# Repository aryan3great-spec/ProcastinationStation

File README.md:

Hello hello hello , this is the start to my hopefully long line of emulators that i hope to perfect to my comfort. 
I love Pokemon hence im here to make a emulator thats gameboy shaped, it is powered by the raspberry pi and i have made 
a custom enclosure for it as well 

I got the inspiration from multiple videos on youtube and also from my friend buying a used new 3ds (terrible naming) and that got me so interested in emulators. From the videos ik that the most cost effiecent and easy to start with sbc is going to be the rpi 02w. 

The only function it has is to run retropie and as many emulators i can fit on a sd card

It has a dpad, abxy, start select and 4 shoulder buttons which should be able to cover emsot games. Which i hope look greaat on the 2.8 inch non touch lcd i've chosen to save cost 

I had some troubles in kicad with locating the buttons equidistant and allign and im certain they arent even symmetric but we'll know soon enough 

i hope to add audio and power in further itterations but idek if i can make the screen work yet so thats why its not as complicated

*THIS WILL BE THE DESIGN OF MY CONSOLE* 

*THIS IS THE PCB DESIGN* 

*THIS IS THE SCHEMATIC*

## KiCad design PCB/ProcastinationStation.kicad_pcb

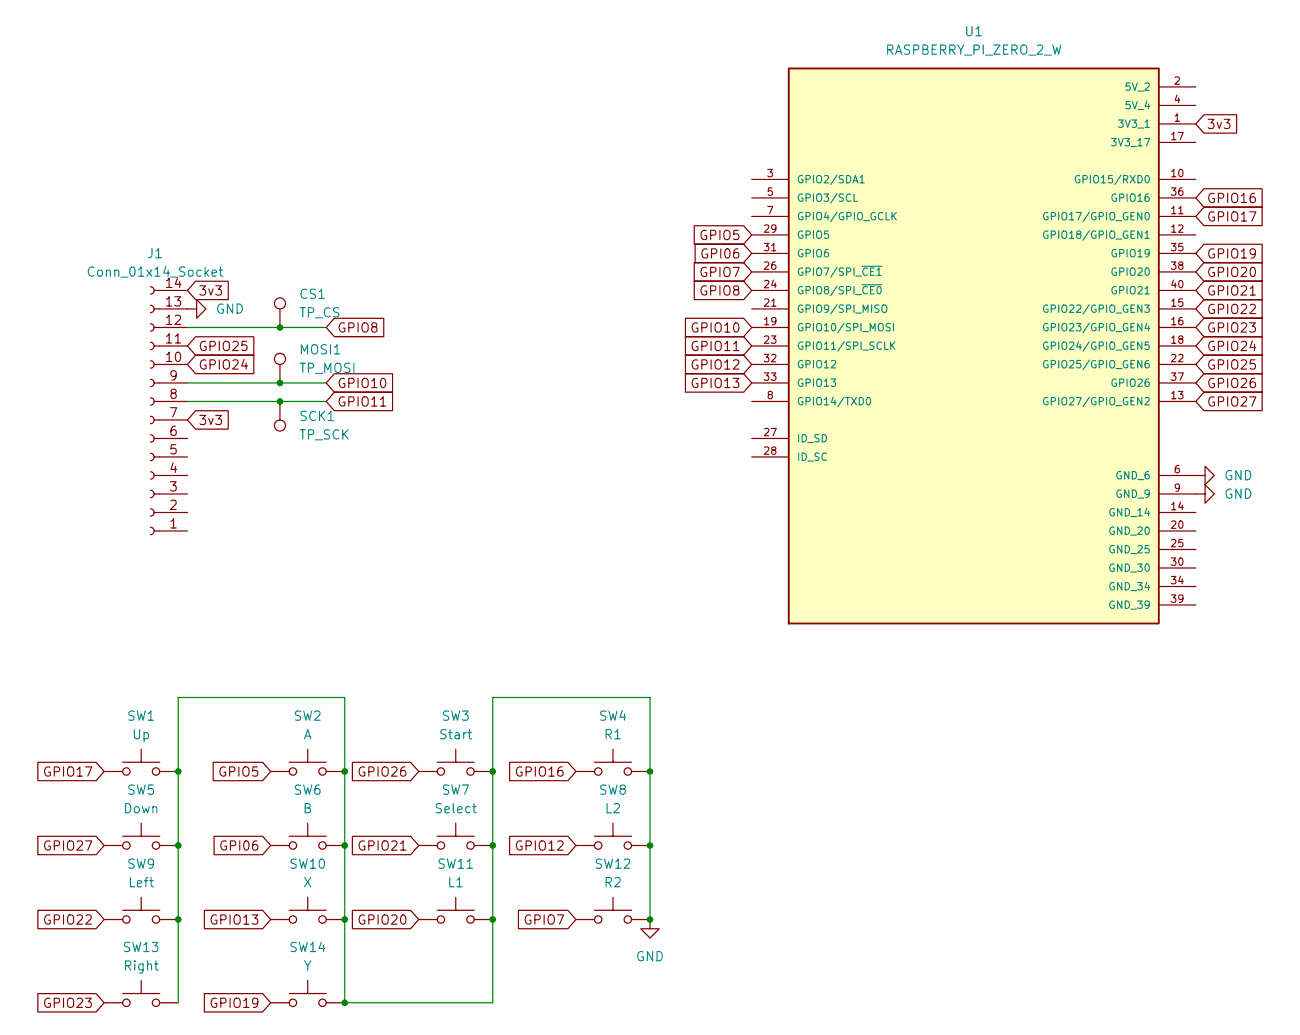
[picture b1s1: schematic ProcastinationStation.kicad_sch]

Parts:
CS1: TP_CS; TestPoint_Pad_D1.0mm
J1: Conn_01x14_Socket; TFT 2.8_ display
MOSI1: TP_MOSI; TestPoint_Pad_D1.0mm
SCK1: TP_SCK; TestPoint_Pad_D1.0mm
SW1: Up; SW_PUSH_6mm_H5mm
SW2: A; SW_PUSH_6mm_H5mm
SW3: Start; SW_PUSH_6mm_H5mm
SW4: R1; SW_PUSH_6mm_H5mm
SW5: Down; SW_PUSH_6mm_H5mm
SW6: B; SW_PUSH_6mm_H5mm
SW7: Select; SW_PUSH_6mm_H5mm
SW8: L2; SW_PUSH_6mm_H5mm
SW9: Left; SW_PUSH_6mm_H5mm
SW10: X; SW_PUSH_6mm_H5mm
SW11: L1; SW_PUSH_6mm_H5mm
SW12: R2; SW_PUSH_6mm_H5mm
SW13: Right; SW_PUSH_6mm_H5mm
SW14: Y; SW_PUSH_6mm_H5mm
U1: RASPBERRY_PI_ZERO_2_W; MODULE_RASPBERRY_PI_ZERO_2_W; PARTREV April 2024

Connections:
3v3: J1.7, J1.14, U1.1 (3V3_1)
GND: J1.13, SW1.2, SW2.2, SW3.2, SW4.2, SW5.2, SW6.2, SW7.2, SW8.2, SW9.2, SW10.2, SW11.2, SW12.2, SW13.2, SW14.2, U1.6 (GND_6), U1.9 (GND_9)
GPI06: SW6.1, U1.31 (GPIO6)
GPIO5: SW2.1, U1.29 (GPIO5)
GPIO7: SW12.1, U1.26 (GPIO7/SPI_~CE1)
GPIO8: CS1.1, J1.12, U1.24 (GPIO8/SPI_~CE0)
GPIO10: J1.9, MOSI1.1, U1.19 (GPIO10/SPI_MOSI)
GPIO11: J1.8, SCK1.1, U1.23 (GPIO11/SPI_SCLK)
GPIO12: SW8.1, U1.32 (GPIO12)
GPIO13: SW10.1, U1.33 (GPIO13)
GPIO16: SW4.1, U1.36 (GPIO16)
GPIO17: SW1.1, U1.11 (GPIO17/GPIO_GEN0)
GPIO19: SW14.1, U1.35 (GPIO19)
GPIO20: SW11.1, U1.38 (GPIO20)
GPIO21: SW7.1, U1.40 (GPIO21)
GPIO22: SW9.1, U1.15 (GPIO22/GPIO_GEN3)
GPIO23: SW13.1, U1.16 (GPIO23/GPIO_GEN4)
GPIO24: J1.10, U1.18 (GPIO24/GPIO_GEN5)
GPIO25: J1.11, U1.22 (GPIO25/GPIO_GEN6)
GPIO26: SW3.1, U1.37 (GPIO26)
GPIO27: SW5.1, U1.13 (GPIO27/GPIO_GEN2)

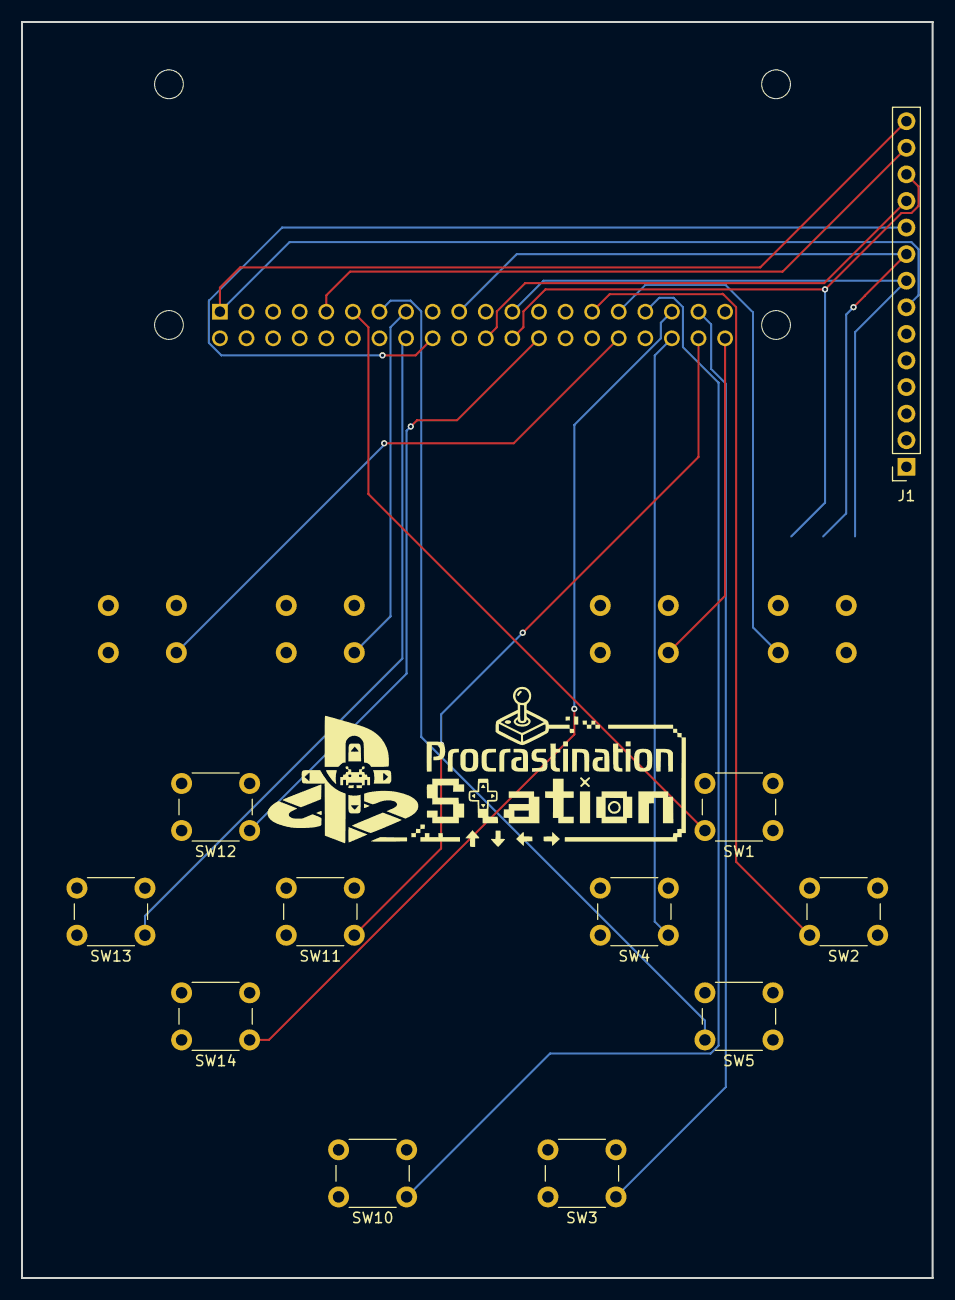
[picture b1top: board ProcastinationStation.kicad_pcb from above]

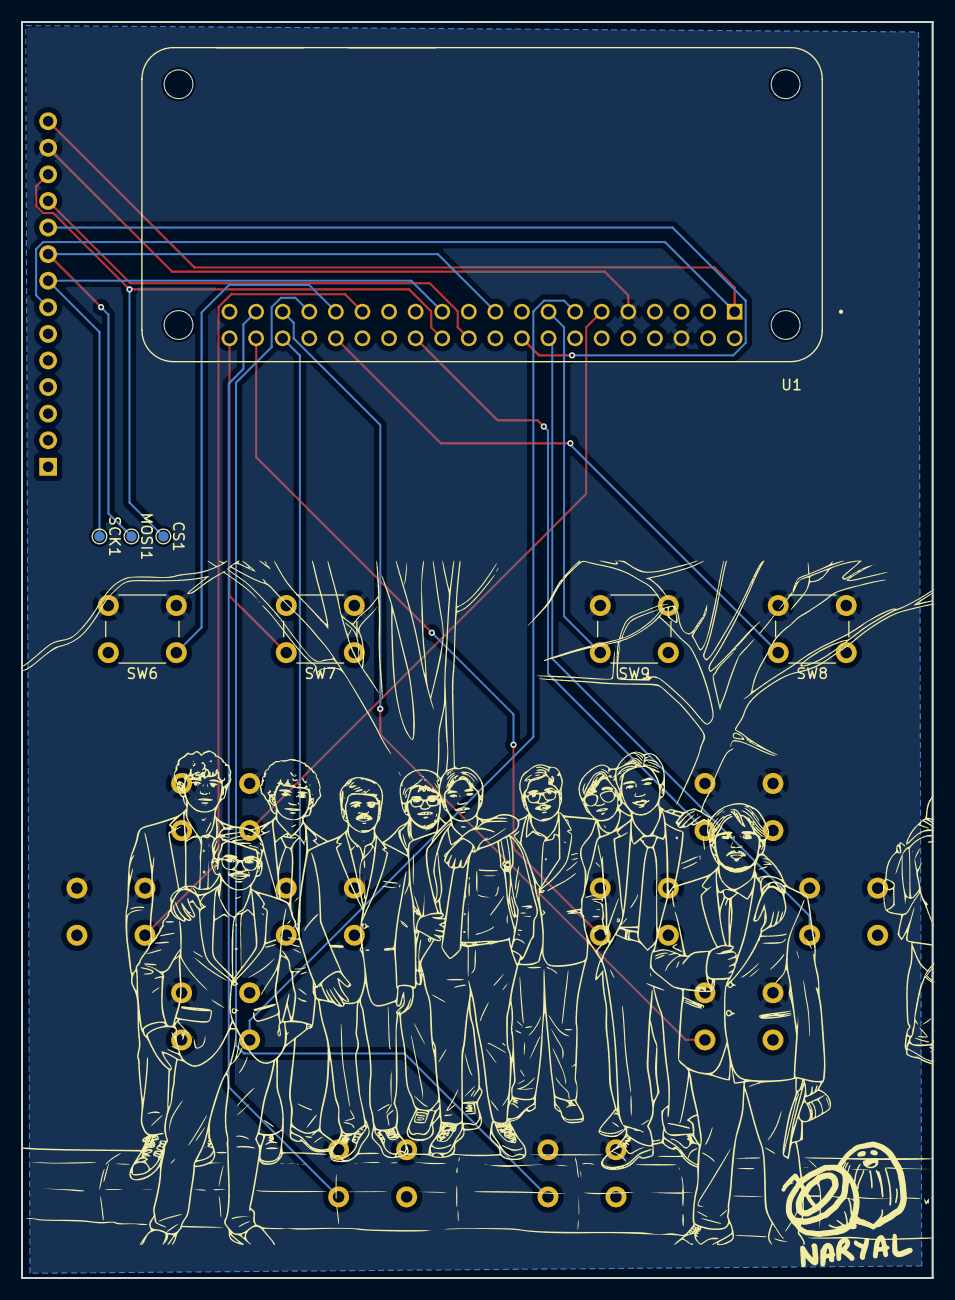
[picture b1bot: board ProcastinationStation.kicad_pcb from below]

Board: 2 copper layers, 87.0 x 120.0 mm, 19 parts (8 on the bottom side), 21 nets.

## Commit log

2026-05-02 Initial commit: PCB, 3D print, and controller code
2026-05-07 Enhance README with project details and inspiration
    Expanded the README to include inspiration, design details, and future plans for the emulator project.
2026-05-07 Update PCB schematic and layout
